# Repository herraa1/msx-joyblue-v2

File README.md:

# Bluetooth controller adapter for MSX (msx-joyblue) v2

Connect Bluetooth controllers to [MSX computers](https://www.msx.org/wiki/)

## Introduction

The msx-joyblue is an adapter that allows connecting Bluetooth controllers to [MSX General Purpose I/O Interfaces](https://www.msx.org/wiki/General_Purpose_port) (aka joystick ports).

The adapter is based on the [unijoysticle2](https://github.com/ricardoquesada/unijoysticle2) and [bluepad32](https://github.com/ricardoquesada/bluepad32) projects, both owned by Ricardo Quesada.

The main features of the msx-joyblue v2 adapter are:
* small size
* made of widely available electronic components
* uses SMD components, so good soldering skills are needed to build the adapter
* emulates up to two MSX joysticks
* attaches to MSX computers using female standard DE9 connectors
* formally requires an external USB power supply as the adapter draws slightly more current than two MSX general purpose I/O interfaces can officially provide
* optionally, can be powered using MSX general purpose I/O interfaces without an external power supply if your MSX can safely supply enough current
* builtin leds provide information about the operation of the adapter

## [Hardware](hardware/kicad/)

The msx-joyblue v2 adapter uses an [ESP32-WROOM-32E chip](https://www.espressif.com/sites/default/files/documentation/esp32-wroom-32e_esp32-wroom-32ue_datasheet_en.pdf) to convert the Bluetooth controller actions to the [MSX joystick standard signalling](https://www.msx.org/wiki/Joystick_control).

A two-sided printed circuit board (PCB) is used to put together all components:
* The ESP32-WROOM-32E bluetooth MCU chip
* A CH340C USB to UART chip, to make it easy to upgrade firmware on the ESP32 chip
* A pair of S8050 NPN transistors to control the boot and enable signals of the ESP32 from the CH340C
* An AMS1117-3.3 regulator to convert the 5V from either the USB port or joystick ports to the 3.3V required by the ESP32 chip
* Four 74LS03 quad 2-input NAND gates with open collectors to completely mimic the standard MSX joystick behavior
* A pair of PTC fuses to minimize damage to the MSX computer in case something goes wrong with the board
* Several additional required components (diodes, leds, resistors, ceramic capacitors and an electrolytic capacitor)
* PH2.0 connectors are used to connect cable extensions
* A 2.0 pitch I2C header is added for future extensions
* Jumpers are provided to enable different power options
* A slider switch is used to enable powering the adapter from the MSX side
* Three momentary push buttons are used to reset the board, swap joysticks or change the operation mode

Connection to the MSX general purpose I/O interfaces is implemented using DE9 joystick extension cables with a female DE9 connector on one side and a loose end on the other side.
The MSX joystick extension cable loose end is wired according to the following pinout mapping.

|  |
|:--|
| MSX joystick connector pinout, from controller plug side |

| MSX side pin | Cable color (may vary) | Signal |
| ------------ | ---------------------- | ------ |
| 5            | Brown                  | +5v    |
| 4            | Orange                 | RIGHT  |
| 3            | Grey                   | LEFT   |
| 2            | Black                  | DOWN   |
| 1            | Red                    | UP     |
| 6            | Green                  | TRIG1  |
| 7            | White                  | TRIG2  |
| 8            | Blue                   | STROBE |
| 9            | Yellow                 | GND    |

> [!WARNING]
> The msx-joyblue v2 adapter uses a different pin order on the PH2.0 header than the msx-joyblue v1 adapter.
>
> Make sure you respect the correct pin order for msx-joyblue-v2.
>

### Recommended Build

Please, use [msx-joyblue-v2 Build2c](#build2c) for making new boards.

You can find ready to order PCBs and the complete BoM at the [PCBWay community site](https://www.pcbway.com/project/shareproject/msx_joyblue_v2_build2c_caa88943.html).

### [Build2c](hardware/kicad/msx-joyblue-v2-build2c)

[Interactive Bill Of Materials (BoM)](https://html-preview.github.io/?url=https://raw.githubusercontent.com/herraa1/msx-joyblue-v2/main/hardware/kicad/msx-joyblue-v2-build2c/bom/ibom.html)

The Build2c adapter implements the following changes since Build2b:
* move capacitor C3 and resistor R1 closer to the ESP32 EN pin
* change C3 from 10uF to 22uF to give extra ramp up time to the 3V3 power rail

|
|:--|
|msx-joyblue-v2 Build2c PCBs front and rear|

||
|:--|
|msx-joyblue-v2 Build2c populated PCB|

### Build2b

> [!NOTE]
> Build2b was never fabricated and has been marked obsolete. Use the [recommended build](#recommended-build) instead.

The Build2b is similar to Build2 but changes slightly some silkscreen text and graphics.

### Build2

> [!NOTE]
> Build2 has been marked obsolete. Use the [recommended build](#recommended-build) instead.

The Build2 adapter mimics completely the standard MSX joystick behavior:

* When pin8 is HIGH, the adapter puts all stick and triggers signals in high impedance mode irrespective of their status (as if stick and triggers were not hold in the standard MSX joystick schematic), which become HIGH on the MSX side via the MSX PSG related circuitry pull-ups (matching the expected behavior)
* When pin8 is LOW
  * if a stick direction or trigger is hold, the corresponding signal is pulled down to GND causing it to be LOW (matching the expected behavior)
  * if a stick direction or trigger is not hold, the corresponding signal is put in high impedance mode, which becomes HIGH on the MSX side via the MSX PSG related circuitry pull-ups (matching the expected behavior)

This build uses discrete logic components to honor the pin8 signaling (four [74LS03DR quad 2-input positive-nand gates with open collector outputs](https://www.ti.com/lit/ds/symlink/sn74ls03.pdf)) and uses open collector outputs which makes the adapter safer [^3] than the standard MSX joystick schematic depicted in the MSX Technical Data Book, as it avoids a series of undesired conditions that can lead to bus contention/short circuits.

|||
|-|-|
|msx-joyblue-v2 Build2 first prototype|msx-joyblue-v2 Build2 first prototype within acrylic case|

## [Firmware](https://github.com/ricardoquesada/bluepad32/tree/main)

The msx-joyblue v2 adapter firmware uses Ricardo Quesada [bluepad32](https://github.com/ricardoquesada/bluepad32/tree/main) library to drive Bluetooth controllers.
A [small modification](https://github.com/ricardoquesada/bluepad32/commit/9736bd169bc13ec625d469b8305d2ed2f46d6e69) to the library that enables support for MSX computers has been already commited to the _main_ branch.

See [bluepad32 documentation](https://github.com/ricardoquesada/bluepad32/tree/main/docs) for [supported Bluetooth controllers](https://github.com/ricardoquesada/bluepad32/blob/main/docs/supported_gamepads.md).

## [Enclosure](enclosure/)

A simple yet functional acrylic enclosure design is included.

## Powering the msx-joyblue adapter

The msx-joyblue adapter uses about ~107mA when operating, while a single MSX general purpose I/O interface is capable of delivering up to 50mA according to the MSX standard [^1].
That means that even using two MSX general purpose I/O interfaces (50mA + 50mA = 100mA) we are slightly over (107mA) the max current specification for the MSX general purpose I/O interfaces.

Thus, the safest way to power the msx-joyblue adapter is by powering it via the USB mini connector of the board using an external 5V USB power supply. The board automatically powers up when using the USB mini connector without enabling any switch.

Nevertheless, even if the MSX especification puts such a low limit on the current that can be drawn from a general purpose I/O interface, real MSX hardware usually can safely deliver enough current for the msx-joyblue adapter to work correctly without harming our beloved classic computers.

Taking that into account, the msx-joyblue adapter has been enabled to be optionally powered by the MSX general purpose I/O interfaces port 1 and port 2.

To enable powering the msx-joyblue adapter from _Port 1_ and/or _Port 2_, the switch SW5 _JOY PWR_ must be first turned on by sliding the switch handle to the right.

> [!NOTE]
> A [1N5819 SMD Schottky diode](https://www.diodes.com/assets/Datasheets/1N5819HW.pdf) D3 is used to avoid leaking current from the msx-joyblue adapter to the MSX in case the msx-joyblue adapter is powered by USB while the _JOY PWR_ switch is ON.
> Another [1N5819 SMD Schottky diode](https://www.diodes.com/assets/Datasheets/1N5819HW.pdf) D2 prevents backpowering the USB side from the MSX side.
> And two Positive Temperature Coeficient (PTC) resettable fuses F1 and F2 of 50mA each protect the MSX general purpose I/O interfaces port 1 and port 2 from excess of current in case something goes horribly wrong on the msx-joyblue adapter side.

To power the msx-joyblue adapter using the MSX general purpose I/O interfaces we must first understand how the PTC protections on the msx-joyblue adapter are implemented.

The selected PTCs are rated for 50mA which is the so called Hold Current (the maximum current that can flow in normal operation). There is also the Trip Current (the minimum current necessary for the PTC to move to high-resistance state) which for the selected PTCs is around 100mA. Those thresholds are dependent on temperature and voltage. And to make things more undeterministic, the behavior of the PTC when current is between those thresholds is undefined (it may trip or not).

In normal operation and for a room temperature of around 25 degrees Celsius, the selected PTCs in practice never trip below 75mA.

> [!NOTE]
> Depending on the exact PTCs installed, the trip current may be slightly different and the adapter may trip at a different point. Unless you buy the PTCs from a reliable source, it is very difficult to know the exact PTC specifications. 
>
> Remember that the PTCs are provided as a safeguard in case something goes really wrong on the adapter, not to act as an exact current limiter to strictly comply with the 50mA per-port MSX specification.

So **if our MSX computer can safely provide more than 50mA on each MSX general purpose I/O interface** (which is usually the case), we can connect both _Port 1_ and _Port 2_ to the MSX computer and turn on the SW5 _JOY PWR_ switch to power the msx-joyblue adapter. Note that we need to connect both ports even if we use just one Bluetooth gamepad, just to meet the power requirements.

Two jumpers JP2 and JP3 can be used to bypass the PTC protections for _Port 1_ and _Port 2_ respectively.

> [!WARNING]
> Bypassing the PTC protections may damage your MSX computer.
> Do not bypass the PTC protections unless you known what you are doing.

By closing JP2 (and/or JP3) and **if our MSX computer can safely provide more than 100mA on a single MSX general purpose I/O interface**, we can connect _Port 1_ (or _Port 2_) to the MSX computer and turn on the SW5 _JOY PWR_ switch to power the msx-joyblue adapter using a single joystick port.

In summary, we can use the following options to power the msx-joyblue adapter (from safest to less safe):
* via the board USB mini conector
  * leave open jumpers JP2 and JP3
  * turn off the SW5 _JOY PWR_ switch
  * connect a 5V USB power supply to the board USB mini connector
* via two MSX general purpose I/O interfaces, if your MSX can safely provide slightly more than 50mA on each MSX general purpose I/O interface
  * leave open jumpers JP2 and JP3
  * turn on the SW5 _JOY PWR_ switch
  * connect both _Port 1_ and _Port 2_ to the MSX general purpose I/O interfaces
* via one MSX general purpose I/O interface, if your MSX can safely provide more than 100mA on each MSX general purpose I/O interface
  * close jumpers JP2 and/or JP3
  * turn on the SW5 _JOY PWR_ switch
  * connect _Port 1_ or _Port 2_ to a MSX general purpose I/O interface

## Switches and Buttons

| **Switch** | **State**      | **Description**                                                          |
|------------|----------------|--------------------------------------------------------------------------|
| _JOYPWR_   | Off            | power from MSX computer via joystick port(s) is off (except logic gates) |
| _JOYPWR_   | On             | board electronics get power from MSX computer via joystick port(s)       |

> [!NOTE]
> If you plug a +5V USB power supply to the USB mini connector, the adapter will turn on unconditionally irrespective of the _JOYPWR_ switch position.
>

| **Button**   | **Description**                                                                             |
|--------------|---------------------------------------------------------------------------------------------|
| MODE         | change the [operation mode](https://github.com/ricardoquesada/unijoysticle2/blob/main/docs/user_guide.md#unijoysticle-buttons-and-leds) of the connected gamepad between "basic mode" and "twin stick mode" |
| SWAP         | swap connected gamepads between MSX joystick ports                                          |
| RESET        | restart the firmware, gamepads get disconnected                                             |

## LED indicators

| **LED**   | **State**      | **Indication** |
|-----------|----------------|---------------|
| _POWER_   | Off            | board is not receiving 3V3 power |
| _POWER_   | Solid Red      | board is receiving 3V3 power     |
| _Port1_   | Off            | no gamepad is controlling _Port 1_ |
| _Port1_   | Solid Green    | a connected gamepad is controlling _Port 1_ |
| _Port1_   | Blinking Green | Every 1sec, PTCs are tripping, see [Troubleshooting](#troubleshooting) |
| _Port2_   | Off            | no gamepad is controlling _Port 2_ |
| _Port2_   | Solid Green    | a connected gamepad is controlling _Port 2_ |
| _BT DISC_ | Off            | Bluetooth discovery is off, no new connections are accepted, existing connections (if any) stay on |
| _BT DISC_ | Solid Blue     | Bluetooth discovery is on, new connections are accepted, both "connects" and "re-connects" are accepted |

See also the [Unijoysticle user guide](https://github.com/ricardoquesada/unijoysticle2/blob/main/docs/user_guide.md#unijoysticle-buttons-and-leds), keeping in mind that led colors are slightly different.

## Troubleshooting

**Q: Just after powering the board _POWER_ led is solid red, _Port2_ and _BT DISC_ leds are off and the _Port1_ led is solid green, but the adapter does not work**

**A:** Press the reset button to reinitialize the adapter, the _BT DISC_ led should go solid blue shortly, when the adapter is ready.

**Q: I did the reset, but now the _Port1_ led blinks every second, the _BT DISC_ led is off and the _Port2_ is solid green but the adapter does not work**

**A:** The PTC fuses are tripping preventing the adapter to properly work. See the [Powering the msx-joyblue adapter](#powering-the-msx-joyblue-adapter) section: use a USB power supply or install the fuse bypass jumpers.

**Q: The _BT DISC_ led went off, what happened?**

**A:** You either have 2 gamepads already connected or have turned on the [_Twin Stick_ mode](https://github.com/ricardoquesada/unijoysticle2/blob/main/docs/user_guide.md#twin-stick-mode-aka-enhanced-mode).

This can happen too if the PTC fuses are tripping (see previous question).

**Q: My Wiimote does not connect**

**A:** If the adapter was previously connected, try pushing any Wiimote button until the Wiimote connects. If that does not work, open the battery compartment and press the red _SYNC_ button to pair the Wiimote with the adapter.

## Compatibility Tests

| **Model**                                                               | **Adapter PCB v2 Build2c** |
|-------------------------------------------------------------------------|----------------------------|
| [Sony MSX HB-101P](https://www.msx.org/wiki/Sony_HB-101P)               |           OK               |
| [Sony MSX HB-501F](https://www.msx.org/wiki/Sony_HB-501F)               |           OK               |
| [Toshiba MSX HX-10P](https://www.msx.org/wiki/Toshiba_HX-10P)           |           OK               |
| [Philips MSX2 VG-8235](https://www.msx.org/wiki/Philips_VG-8235)        |           OK               |
| [Panasonic MSX2+ FS-A1WSX](https://www.msx.org/wiki/Panasonic_FS-A1WSX) |           OK               |
| [Omega MSX2+](https://github.com/skiselev/omega)                        |           OK               |
| [MSXVR](https://msxvr.com/en/)                                          |           OK               |
| [Tides Rider](https://genami.shop/products/tides-rider-hdk)             |           OK               |
| [JFF-TMSHAT](https://github.com/herraa1/JFF-TMSHAT)                     |           OK               |

## Build Instructions

Follow these [Build instructions](Build.md) in order to assemble the msx-joyblue v2 adapter.

## References

Ricardo Quesada bluepad32 library
* https://github.com/ricardoquesada/bluepad32

Ricardo Quesada Unijoysticle2 project
* https://github.com/ricardoquesada/unijoysticle2

MSX general purpose I/O interface
* https://www.msx.org/wiki/General_Purpose_port

[^1]: https://www.msx.org/wiki/General_Purpose_port
[^2]: https://www.msx.org/wiki/MSX-HID
[^3]: https://www.msx.org/wiki/Joystick/joypad_controller (see "Undesired Conditions")

## Image Sources

* https://www.oshwa.org/open-source-hardware-logo/
* https://en.wikipedia.org/wiki/File:Numbered_DE9_Diagram.svg
* https://commons.wikimedia.org/wiki/File:Bluetooth.svg

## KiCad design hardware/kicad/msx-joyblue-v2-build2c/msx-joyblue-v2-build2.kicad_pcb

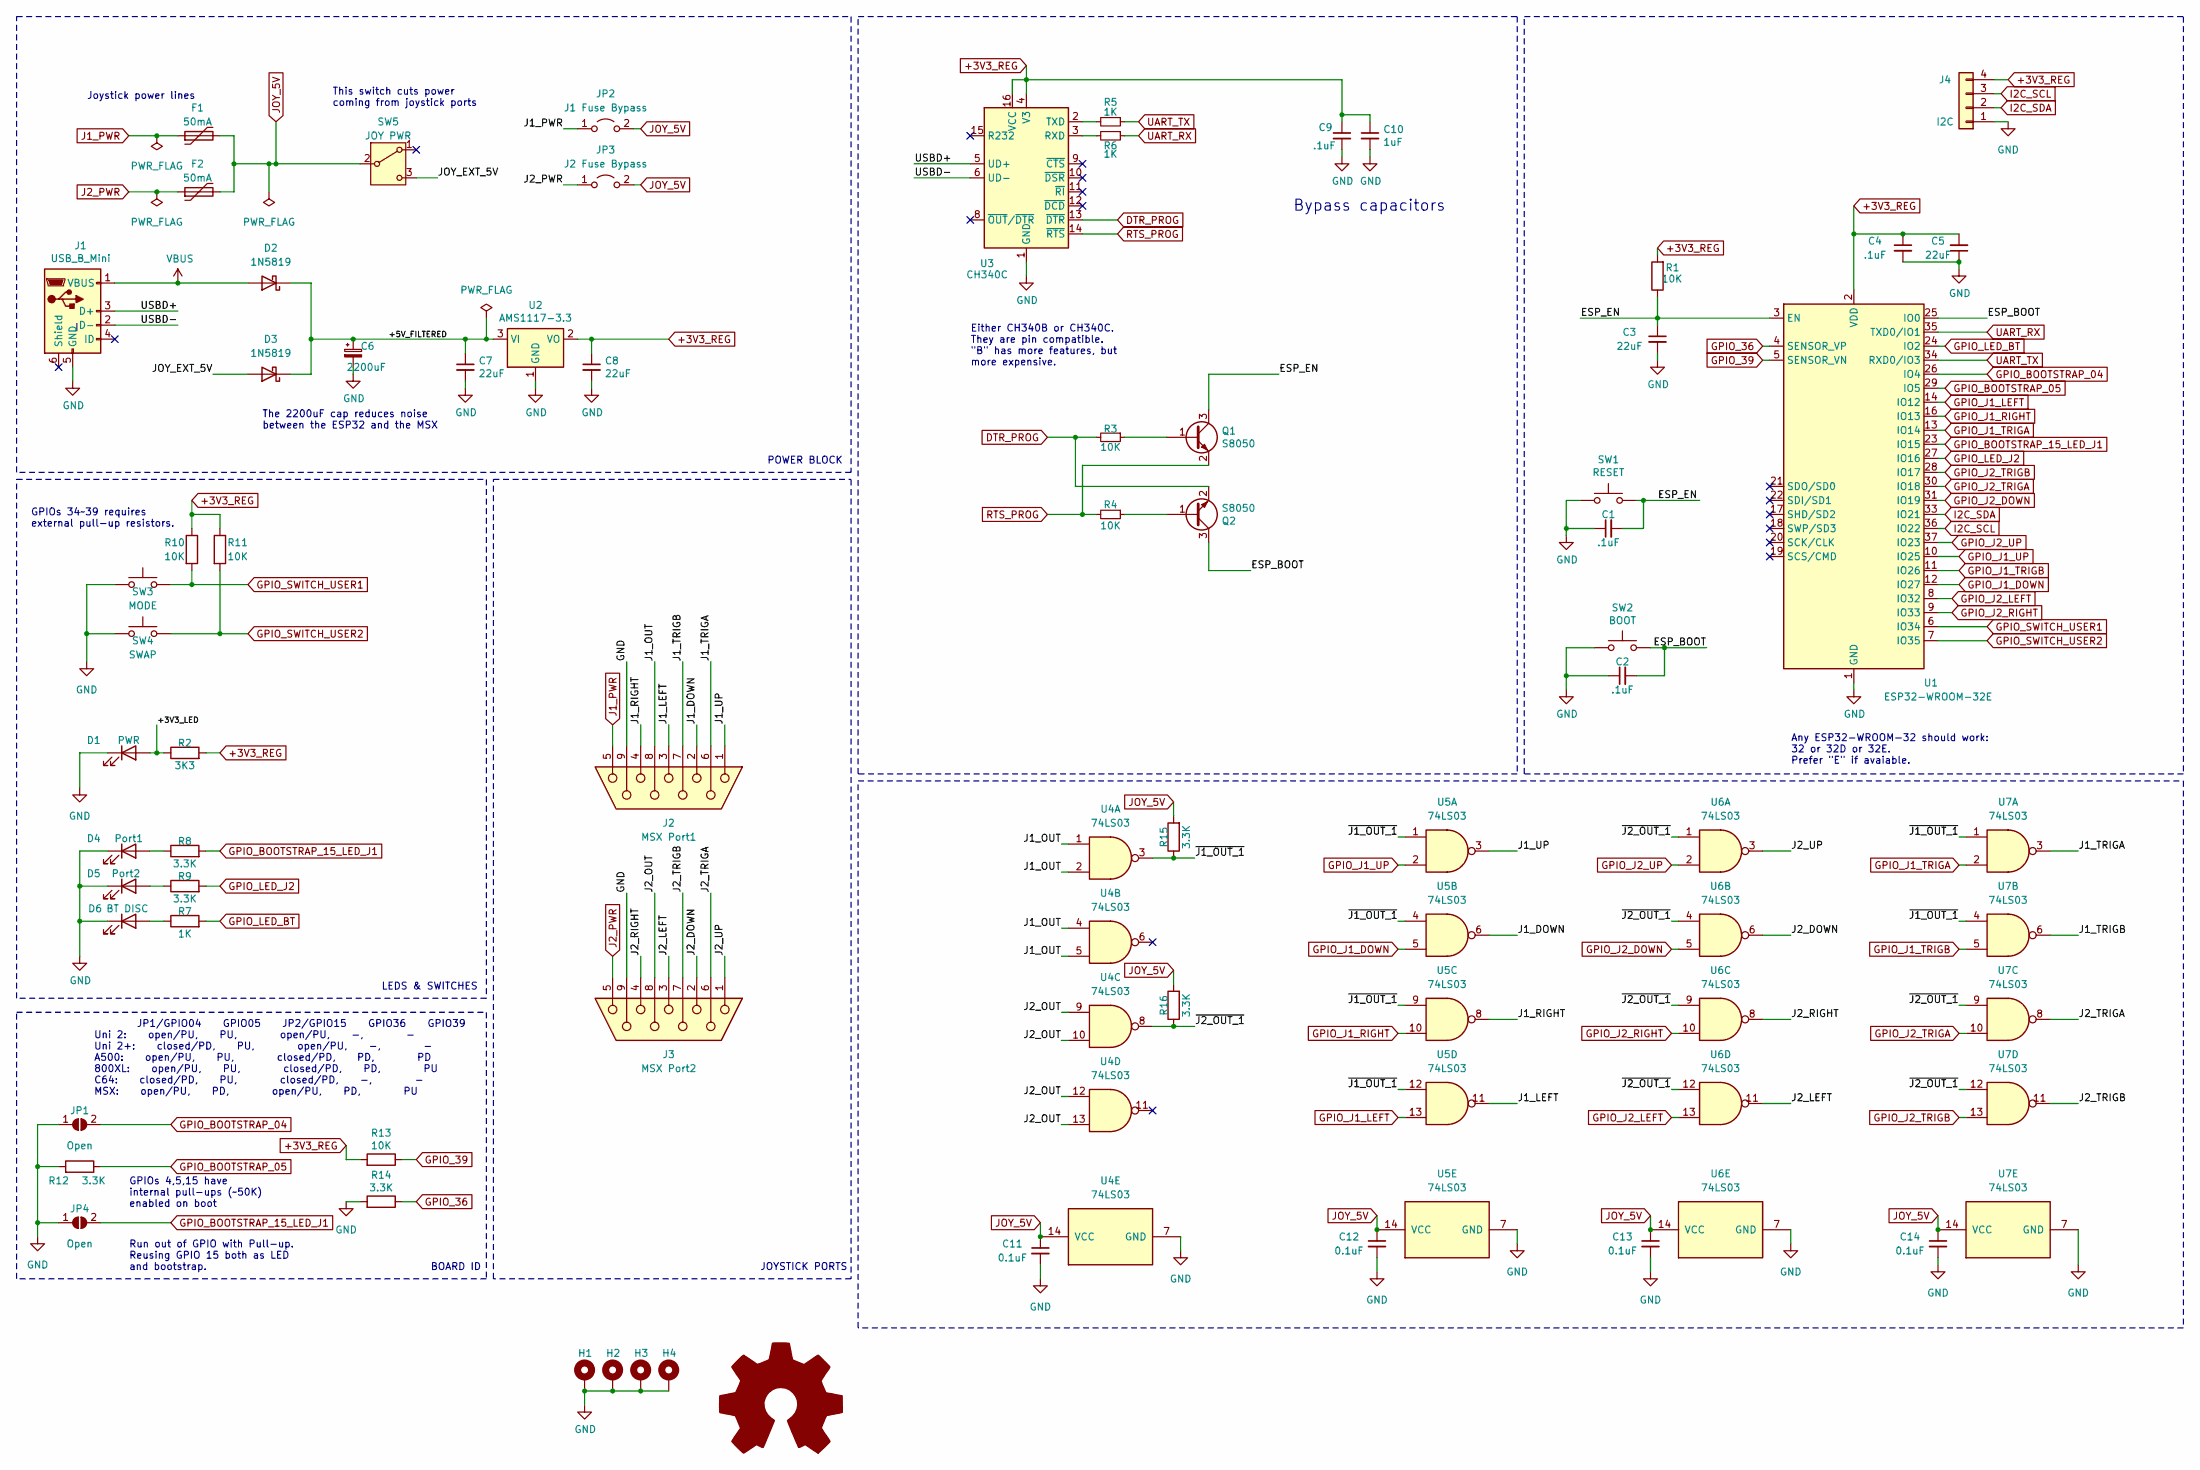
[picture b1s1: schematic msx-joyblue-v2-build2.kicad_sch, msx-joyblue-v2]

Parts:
C1, C2, C4, C9: .1uF; C_0805_2012Metric_Pad1.18x1.45mm_HandSolder
C3, C5, C7, C8: 22uF; C_0805_2012Metric_Pad1.18x1.45mm_HandSolder
C6: 2200uF; CP_Elec_10x10.5
C10: 1uF; C_0805_2012Metric_Pad1.18x1.45mm_HandSolder
C11, C12, C13, C14: 0.1uF; C_0805_2012Metric_Pad1.18x1.45mm_HandSolder
D1: PWR; LED_0805_2012Metric_Pad1.15x1.40mm_HandSolder
D2, D3: 1N5819; D_SOD-123
D4: Port1; LED_0805_2012Metric_Pad1.15x1.40mm_HandSolder
D5: Port2; LED_0805_2012Metric_Pad1.15x1.40mm_HandSolder
D6: BT DISC; LED_0805_2012Metric_Pad1.15x1.40mm_HandSolder
F1, F2: 50mA; Fuse_1206_3216Metric_Pad1.42x1.75mm_HandSolder
H1, H2, H3, H4: MountingHole_Pad; Hole_3mm
J1: USB_B_Mini; USB_Mini-B_Lumberg_2486_01_Horizontal
J2: MSX Port1; JST_PH_S9B-PH-K_1x09_P2.00mm_Horizontal
J3: MSX Port2; JST_PH_S9B-PH-K_1x09_P2.00mm_Horizontal
J4: I2C; JST_PH_B4B-PH-K_1x04_P2.00mm_Vertical
JP1, JP4: Open; SolderJumper-2_P1.3mm_Open_RoundedPad1.0x1.5mm
JP2: J1 Fuse Bypass; PinHeader_1x02_P2.54mm_Vertical
JP3: J2 Fuse Bypass; PinHeader_1x02_P2.54mm_Vertical
Q1, Q2: S8050; SOT-23
R1, R3, R4, R10, R11, R13: 10K; R_0805_2012Metric_Pad1.20x1.40mm_HandSolder
R2: 3K3; R_0805_2012Metric_Pad1.20x1.40mm_HandSolder
R5, R6: 1K; R_0805_2012Metric_Pad1.20x1.40mm_HandSolder
R7: 1K; R_0805_2012Metric_Pad1.20x1.40mm_HandSolder; LCSC C4310
R8, R9, R15, R16: 3.3K; R_0805_2012Metric_Pad1.20x1.40mm_HandSolder; LCSC C4310
R12, R14: 3.3K; R_0805_2012Metric_Pad1.20x1.40mm_HandSolder
SW1: RESET; SW_Tactile_SPST_Angled_PTS645Vx39-2LFS
SW2: BOOT; SW_Push_1P1T_NO_5.1x5.1mm
SW3: MODE; SW_Tactile_SPST_Angled_PTS645Vx39-2LFS
SW4: SWAP; SW_Tactile_SPST_Angled_PTS645Vx39-2LFS
SW5: JOY PWR; SW_SK-12D07G6-1P2T-6mm
SYM1: Logo_Open_Hardware_Large; OSHW-Logo_7.5x8mm_SilkScreen
U1: ESP32-WROOM-32E; ESP32-WROOM-32; LCSC C701341
U2: AMS1117-3.3; SOT-223-3_TabPin2
U3: CH340C; SOIC-16_3.9x9.9mm_P1.27mm
U4, U5, U6, U7: 74LS03; SOIC-14_3.9x8.7mm_P1.27mm

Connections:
+3V3_REG: C4.1, C5.2, C8.1, C9.1, C10.1, J4.4, R1.2, R2.2, R10.1, R11.1, R13.2, U1.2 (VDD), U2.2 (VO), U3.4 (V3), U3.16 (VCC)
/+3V3_LED: D1.2 (A), R2.1
/+5V_FILTERED: C6.1, C7.1, D2.1 (K), D3.1 (K), U2.3 (VI)
/ESP_BOOT: C2.2, Q2.3 (C), SW2.2, U1.25 (IO0)
/ESP_EN: C1.2, C3.1, Q1.3 (C), R1.1, SW1.2, U1.3 (EN)
/J1_DOWN: J2.2, U5.6
/J1_LEFT: J2.3, U5.11
/J1_OUT: J2.8, U4.1, U4.2, U4.4, U4.5
/J1_RIGHT: J2.4, U5.8
/J1_TRIGA: J2.6, U7.3
/J1_TRIGB: J2.7, U7.6
/J1_UP: J2.1, U5.3
/J2_DOWN: J3.2, U6.6
/J2_LEFT: J3.3, U6.11
/J2_OUT: J3.8, U4.9, U4.10, U4.12, U4.13
/J2_RIGHT: J3.4, U6.8
/J2_TRIGA: J3.6, U7.8
/J2_TRIGB: J3.7, U7.11
/J2_UP: J3.1, U6.3
/JOY_EXT_5V: D3.2 (A), SW5.3 (C)
/USBD+: J1.3 (D+), U3.5 (UD+)
/USBD-: J1.2 (D-), U3.6 (UD-)
/~J1_OUT_1: R15.1, U4.3, U5.1, U5.4, U5.9, U5.12, U7.1, U7.4
/~J2_OUT_1: R16.1, U4.8, U6.1, U6.4, U6.9, U6.12, U7.9, U7.12
DTR_PROG: Q2.2 (E), R3.2, U3.13 (~DTR)
GND: C1.1, C2.1, C3.2, C4.2, C5.1, C6.2, C7.2, C8.2, C9.2, C10.2, C11.2, C12.2, C13.2, C14.2, D1.1 (K), D4.1 (K), D5.1 (K), D6.1 (K), H1.1, H2.1, H3.1, H4.1, J1.5 (GND), J2.9, J3.9, J4.1, JP1.1 (A), JP4.1 (A), R12.2, R14.2, SW1.1, SW2.1, SW3.1, SW4.1, U1.1 (GND), U1.15 (GND), U1.38 (GND), U1.39 (GND), U2.1 (GND), U3.1 (GND), U4.7 (GND), U5.7 (GND), U6.7 (GND), U7.7 (GND)
GPIO_36: R14.1, U1.4 (SENSOR_VP)
GPIO_39: R13.1, U1.5 (SENSOR_VN)
GPIO_BOOTSTRAP_04: JP1.2 (B), U1.26 (IO4)
GPIO_BOOTSTRAP_05: R12.1, U1.29 (IO5)
GPIO_BOOTSTRAP_15_LED_J1: JP4.2 (B), R8.2, U1.23 (IO15)
GPIO_J1_DOWN: U1.12 (IO27), U5.5
GPIO_J1_LEFT: U1.14 (IO12), U5.13
GPIO_J1_RIGHT: U1.16 (IO13), U5.10
GPIO_J1_TRIGA: U1.13 (IO14), U7.2
GPIO_J1_TRIGB: U1.11 (IO26), U7.5
GPIO_J1_UP: U1.10 (IO25), U5.2
GPIO_J2_DOWN: U1.31 (IO19), U6.5
GPIO_J2_LEFT: U1.8 (IO32), U6.13
GPIO_J2_RIGHT: U1.9 (IO33), U6.10
GPIO_J2_TRIGA: U1.30 (IO18), U7.10
GPIO_J2_TRIGB: U1.28 (IO17), U7.13
GPIO_J2_UP: U1.37 (IO23), U6.2
GPIO_LED_BT: R7.2, U1.24 (IO2)
GPIO_LED_J2: R9.2, U1.27 (IO16)
GPIO_SWITCH_USER1: R10.2, SW3.2, U1.6 (IO34)
GPIO_SWITCH_USER2: R11.2, SW4.2, U1.7 (IO35)
I2C_SCL: J4.3, U1.36 (IO22)
I2C_SDA: J4.2, U1.33 (IO21)
J1_PWR: F1.1, J2.5, JP2.1 (A)
J2_PWR: F2.1, J3.5, JP3.1 (A)
JOY_5V: C11.1, C12.1, C13.1, C14.1, F1.2, F2.2, JP2.2 (B), JP3.2 (B), R15.2, R16.2, SW5.2 (B), U4.14 (VCC), U5.14 (VCC), U6.14 (VCC), U7.14 (VCC)
unnamed: D4.2 (A), R8.1
unnamed: D5.2 (A), R9.1
unnamed: D6.2 (A), R7.1
unnamed: Q1.1 (B), R3.1
unnamed: Q2.1 (B), R4.1
unnamed: R6.2, U3.3 (RXD)
unnamed: R5.2, U3.2 (TXD)
RTS_PROG: Q1.2 (E), R4.2, U3.14 (~RTS)
UART_RX: R6.1, U1.35 (TXD0/IO1)
UART_TX: R5.1, U1.34 (RXD0/IO3)
VBUS: D2.2 (A), J1.1 (VBUS)

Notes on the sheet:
JP1/GPIO04 GPIO05 JP2/GPIO15 GPIO36 GPIO39 Uni 2: open/PU, PU, open/PU, -, - Uni 2+: closed/PD, PU, open/PU, -, - A500: open/PU, PU, closed/PD, PD, PD 800XL: open/PU, PU, closed/PD, PD, PU C64: closed/PD, PU, closed/PD, -, - MSX: open/PU, PD, open/PU, PD, PU
This switch cuts power coming from joystick ports
GPIOs 4,5,15 have internal pull-ups (~50K) enabled on boot
BOARD ID
Joystick power lines
GPIOs 34~39 requires external pull-up resistors.
POWER BLOCK
JOYSTICK PORTS
Bypass capacitors
Run out of GPIO with Pull-up. Reusing GPIO 15 both as LED and bootstrap.
LEDS & SWITCHES
Either CH340B or CH340C. They are pin compatible. "B" has more features, but more expensive.
Any ESP32-WROOM-32 should work: 32 or 32D or 32E. Prefer "E" if avaiable.
The 2200uF cap reduces noise between the ESP32 and the MSX

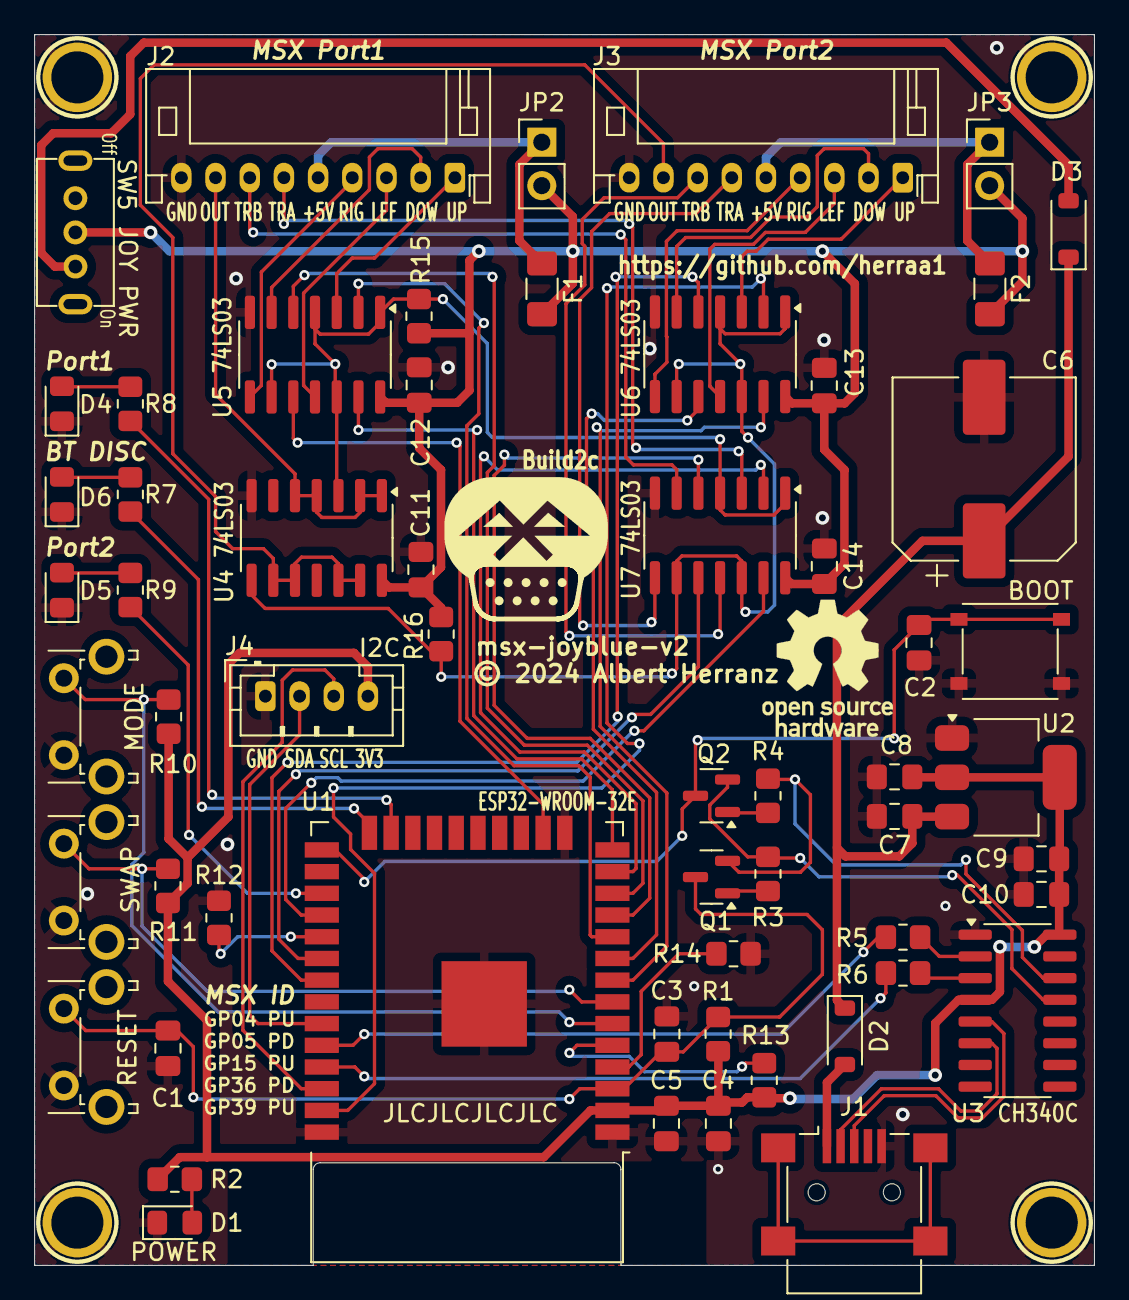
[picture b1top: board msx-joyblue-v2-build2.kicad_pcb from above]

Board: 2 copper layers, 62.0 x 72.0 mm, 63 parts (0 on the bottom side), 62 nets.

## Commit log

2024-04-04 Initial commit.
2024-04-04 Fix BoM links
2024-04-04 Fix (maybe) BoM links
2024-04-05 readme: redaction fixes
2024-04-05 readme: add info about PTC intended use and specifications variability
2024-04-05 add smallish image for direct linking
2024-04-05 zoom smallish image
2024-04-05 updated compatibility tests
2024-04-06 enclosure: rework design, fix strain relief holes
2024-04-18 add Build2c
2024-04-18 enclosure: rework
2024-04-27 enclosure and build2c updates
2024-04-27 readme: acrylic enclosure is ready to use
2024-05-02 add initial build instructions
2024-05-06 readme: leds, buttons and compatibility tests updates
2024-05-06 readme: minimize build2b info, rework build2c images and fix small typo
2024-05-11 build: add test instructions for ESP32
2024-05-19 build: add images for buiding cables
2024-05-25 build: add test instructions for 74LS03
2024-06-08 build: grammar, add 74ls03 test jug image
2024-12-25 readme: reorder builds newest first, mark obsoleted builds
2025-09-17 readme: add reference to new BoM at PCBWay
2025-09-17 readme: update compatibility tests

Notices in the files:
hardware/kicad/msx-joyblue-v2-build2c/msx-joyblue-v2-build2.kicad_pcb:
© 2024 Albert Herranz
